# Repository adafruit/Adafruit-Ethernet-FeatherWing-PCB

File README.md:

## Adafruit Ethernet FeatherWing PCB
<a href="http://www.adafruit.com/products/3201"><br/>
Click here to purchase one from the Adafruit shop</a>

Wireless is wonderful, but sometimes you want the strong reliability of a wire. If your Feather board is going to be part of a permanent installation, this Ethernet FeatherWing will let you add quick and easy wired Internet. Just plug in a standard ethernet cable, and run the Ethernet2 library for cross-platform networking. Works with all/any of our Feather boards as an Ethernet Client (server not supported at this time)!

Ethernet is a tried-and-true networking standard. It's supported by every hub and switch, and because there's a physical connection you don't have to noodle around with SSIDs, passwords, authentication schemes or antennas. It works great with any of our Feathers, the WIZ5500 chip communicates over SPI plus a single CS pin. The Arduino Ethernet2 library works great, and within a few seconds after connecting, will do the DHCP setup for you. As a nice extra, the RJ-45 jack has both link and activity lights that will light/blink to let you know the current connection status.

PCB files for the Adafruit  Ethernet FeatherWing. The format is EagleCAD schematic and board layout
- https://www.adafruit.com/products/3201

### License

Adafruit invests time and resources providing this open source design, please support Adafruit and open-source hardware by purchasing products from [Adafruit](https://www.adafruit.com)!

All text above must be included in any redistribution

Designed by Limor Fried/Ladyada for Adafruit Industries.
Creative Commons Attribution/Share-Alike, all text above must be included in any redistribution. 
See license.txt for additional information.

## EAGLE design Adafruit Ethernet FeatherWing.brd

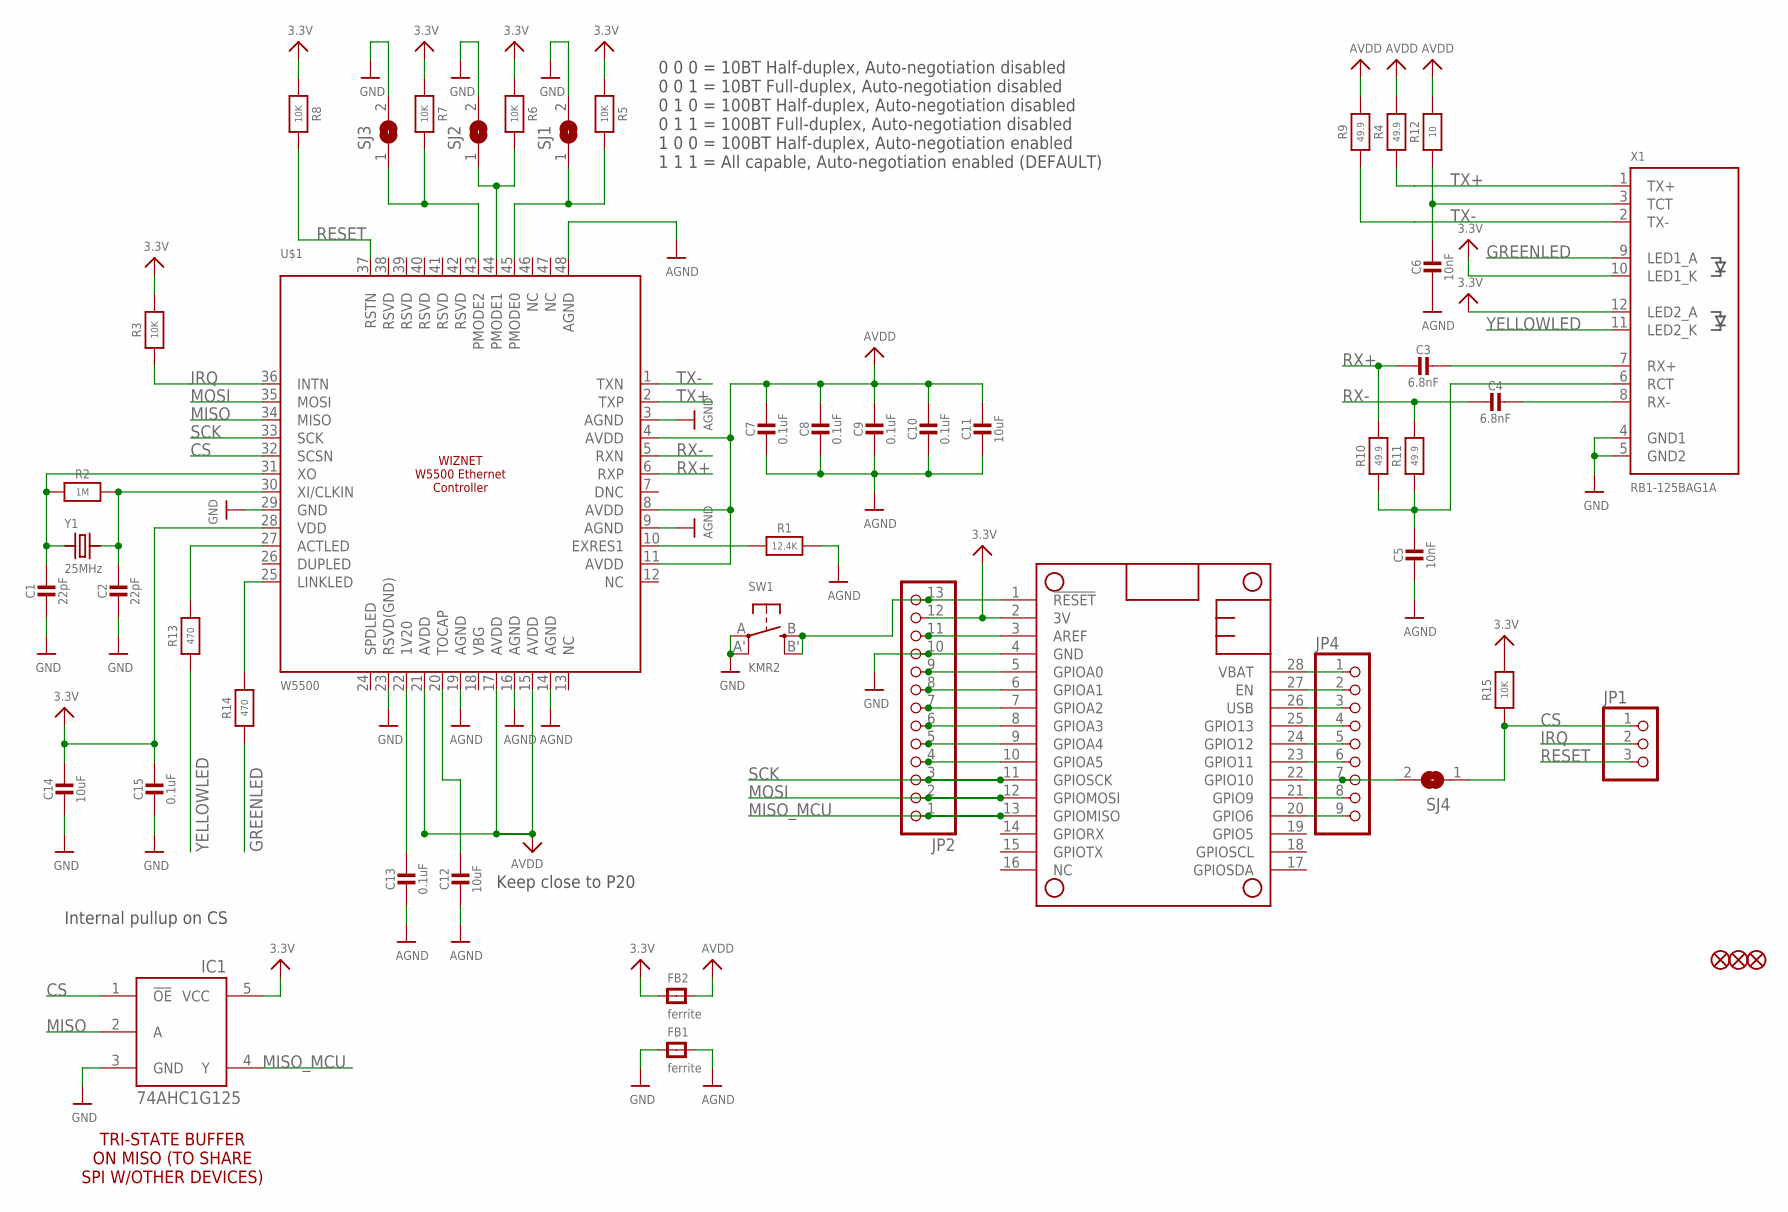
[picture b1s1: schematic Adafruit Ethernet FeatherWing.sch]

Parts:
C1, C2: 22pF; 0603-NO
C3, C4: 6.8nF; 0603-NO
C5, C6: 10nF; 0603-NO
C7, C8, C9, C10, C13, C15: 0.1uF; 0603-NO
C11, C12, C14: 10uF; 0805-NO
FB1, FB2: ferrite; 0805-NO
FID1, FID2, FID3: FIDUCIAL""; FIDUCIAL_1MM
IC1: 74AHC1G125; SOT23-5L
JP1: HEADER-1X376MIL; 1X03_ROUND_76
JP2: HEADER-1X13; 1X13_ROUND_70
JP4: HEADER-1X970MIL; 1X09_ROUND_70
MS1: FEATHERWING_NODIM
R1: 12.4K; 0603-NO
R2: 1M; 0603-NO
R3, R5, R6, R7, R8, R15: 10K; 0603-NO
R4, R9, R10, R11: 49.9; 0603-NO
R12: 10; 0603-NO
R13, R14: 470; 0603-NO
SJ1, SJ2, SJ3: SOLDERJUMPERREFLOW_NOPASTE; SOLDERJUMPER_REFLOW_NOPASTE
SJ4: SOLDERJUMPERCLOSED; SOLDERJUMPER_CLOSEDWIRE
SW1: KMR2; BTN_KMR2_4.6X2.8
U$1: W5500; LQFP48
X1: RB1-125BAG1A; RJ45_PULSEJACK
Y1: 25MHz; CRYSTAL_3.2X2.5

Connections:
3.3V: C14.1, C15.1, FB2.1, IC1.5 (VCC), JP2.12, MS1.2 (3V), R3.2, R5.1, R6.1, R7.1, R8.1, R15.2, U$1.28 (VDD), X1.10 (LED1_K), X1.12 (LED2_A)
AGND: C5.2, C6.2, C7.2, C8.2, C9.2, C10.2, C11.2, C12.2, C13.2, FB1.2, R1.2, U$1.3 (AGND), U$1.9 (AGND), U$1.14 (AGND), U$1.16 (AGND), U$1.19 (AGND), U$1.48 (AGND)
AVDD: C7.1, C8.1, C9.1, C10.1, C11.1, FB2.2, R4.2, R9.2, R12.2, U$1.4 (AVDD), U$1.8 (AVDD), U$1.11 (AVDD), U$1.15 (AVDD), U$1.17 (AVDD), U$1.21 (AVDD)
CS: IC1.1 (!OE), JP1.1, R15.1, SJ4.1, U$1.32 (SCSN)
GND: C1.2, C2.2, C14.2, C15.2, FB1.1, IC1.3 (GND), JP2.10, MS1.4 (GND), SJ1.2, SJ2.2, SJ3.2, SW1.A, SW1.A' (P1), U$1.23 (RSVD(GND)), U$1.29 (GND), X1.4 (GND1), X1.5 (GND2)
GREENLED: R14.1, X1.9 (LED1_A)
IRQ: JP1.2, R3.1, U$1.36 (INTN)
MISO: IC1.2 (A), U$1.34 (MISO)
MISO_MCU: IC1.4 (Y), JP2.1, MS1.13 (GPIOMISO)
MOSI: JP2.2, MS1.12 (GPIOMOSI), U$1.35 (MOSI)
unnamed: C1.1, R2.1, U$1.31 (XO), Y1.1
unnamed: C2.1, R2.2, U$1.30 (XI/CLKIN), Y1.2
unnamed: R1.1, U$1.10 (EXRES1)
unnamed: R5.2, SJ1.1, U$1.45 (PMODE0)
unnamed: R6.2, SJ2.1, U$1.44 (PMODE1)
unnamed: R7.2, SJ3.1, U$1.43 (PMODE2)
unnamed: C3.1, X1.7 (RX+)
unnamed: C4.1, X1.8 (RX-)
unnamed: C5.1, R10.1, R11.1, X1.6 (RCT)
unnamed: C6.1, R12.1, X1.3 (TCT)
unnamed: C13.1, U$1.22 (1V20)
unnamed: C12.1, U$1.20 (TOCAP)
unnamed: R13.2, U$1.27 (ACTLED)
unnamed: R14.2, U$1.25 (LINKLED)
unnamed: JP4.2, MS1.27 (EN)
unnamed: JP4.4, MS1.25 (GPIO13)
unnamed: JP4.5, MS1.24 (GPIO12)
unnamed: JP4.6, MS1.23 (GPIO11)
unnamed: JP4.7, MS1.22 (GPIO10), SJ4.2
unnamed: JP4.8, MS1.21 (GPIO9)
unnamed: JP4.9, MS1.20 (GPIO6)
unnamed: JP2.13, MS1.1 (!RESET), SW1.B (S), SW1.B' (S1)
unnamed: JP2.4, MS1.10 (GPIOA5)
unnamed: JP2.5, MS1.9 (GPIOA4)
unnamed: JP2.6, MS1.8 (GPIOA3)
unnamed: JP2.7, MS1.7 (GPIOA2)
unnamed: JP2.8, MS1.6 (GPIOA1)
unnamed: JP2.9, MS1.5 (GPIOA0)
unnamed: JP2.11, MS1.3 (AREF)
RESET: JP1.3, R8.2, U$1.37 (RSTN)
RX+: C3.2, R10.2, U$1.6 (RXP)
RX-: C4.2, R11.2, U$1.5 (RXN)
SCK: JP2.3, MS1.11 (GPIOSCK), U$1.33 (SCK)
TX+: R4.1, U$1.2 (TXP), X1.1 (TX+)
TX-: R9.1, U$1.1 (TXN), X1.2 (TX-)
USB: JP4.3, MS1.26 (USB)
VBAT: JP4.1, MS1.28 (VBAT)
YELLOWLED: R13.1, X1.11 (LED2_K)

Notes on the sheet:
0 0 0 = 10BT Half-duplex, Auto-negotiation disabled 0 0 1 = 10BT Full-duplex, Auto-negotiation disabled 0 1 0 = 100BT Half-duplex, Auto-negotiation disabled 0 1 1 = 100BT Full-duplex, Auto-negotiation disabled 1 0 0 = 100BT Half-duplex, Auto-negotiation enabled 1 1 1 = All capable, Auto-negotiation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
Internal pullup on CS
Keep close to P20
TRI-STATE BUFFER ON MISO (TO SHARE SPI W/OTHER DEVICES)

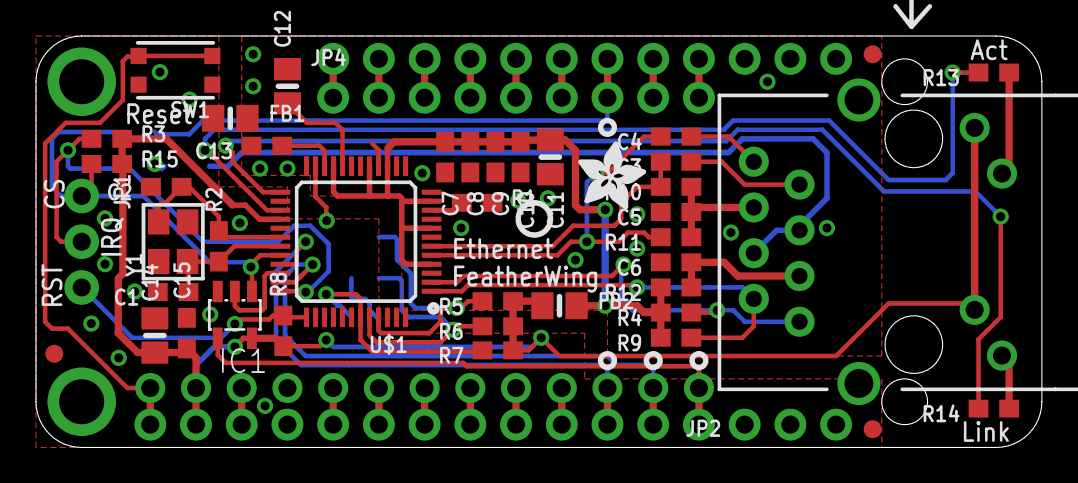
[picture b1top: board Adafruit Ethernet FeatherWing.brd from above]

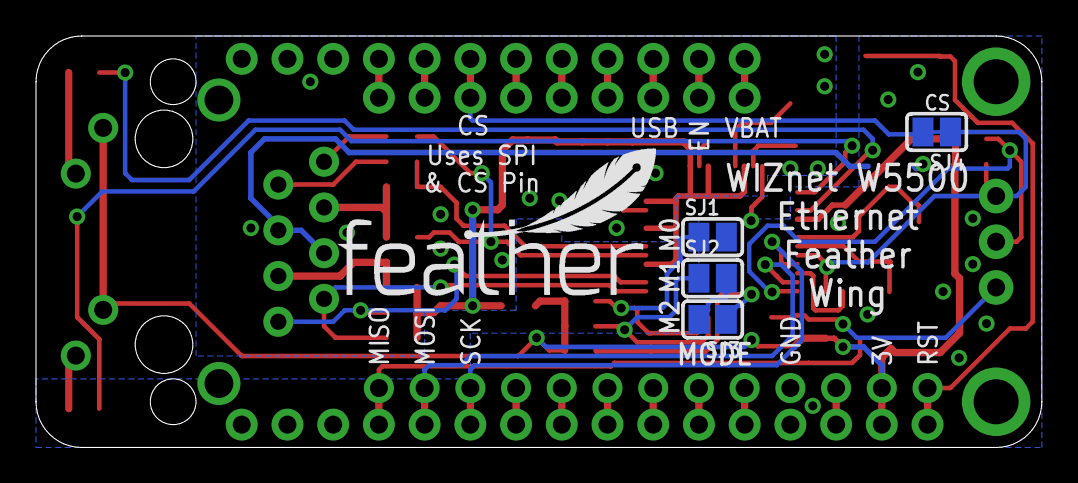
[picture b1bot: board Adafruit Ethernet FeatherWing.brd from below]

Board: 2 copper layers, 55.9 x 22.9 mm, 51 parts (5 on the bottom side), 48 nets.

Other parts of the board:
U$45: PCBFEAT-REV-040
U$48: FEATHERLOGO_MED
U$49: ADAFRUIT_3.5MM

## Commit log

2016-07-27 ethinit

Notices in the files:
parts and their libraries:
microbuilder: This work is placed in the public domain, and may be freely used for commercial and non-commercial work with the following conditions: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
